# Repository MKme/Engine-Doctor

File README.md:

<p align="center">
<b>ESP32 Engine Doctor</b><br>
Use your smartphone web browser to view engine performance and sensor data<br><br>
<br>🐦 <a href="https://twitter.com/mkmeorg">Twitter</a>
| 📺 <a href="https://www.youtube.com/mkmeorg">YouTube</a>
| 🌍 <a href="http://www.mkme.org">mkme.org</a><br>
<br>
Support this project and become a patron on <a href="https://www.patreon.com/EricWilliam">Patreon</a>.<br>
Chat: <a href="https://discord.gg/j9S4Fgv">Discord</a></b>!
</p>

# DIY ESP32 Engine monitoring for all internal combustion engines 
Engine Doc for all chainsaws, small engines and automotive.  

Buy a kit on my store here: https://store.mkme.org/?product=diy-engine-doctor-esp32-egt-engine-tuning-temp-kit

## Use Case:
The original ideea is to use this for performance chainsaw tuning by monitoring the EGT (exhaust gas temp) or cylinder/head temp we have valuable information 
we can use to track/correlate our changes and even monitor saws with autotune or needs. 

## Description:

An ESP32 microcontroller with a high temp thermocouple interface you can mount in or stick to any surface you want to measure. 

The ESP32 makes its own Wifi AP (shows up as Engine Doctor wifi network) you can log in to with your phone- open any browser to the IP in the pic and it will graph the data real time asynchronously on the web page as long as its powered on.  

Also has a separate BME280 temp/baro and humidity sensor that will be in the box enclosure or you could remote mount it in an airbox or anywhere you desire.

Future Expansion- I may make a one-wire inductive tachometer pickup too which will be interrupt driven and may need amp circuit. All the spare GPIO are broken out on the PCB for this. 
Lipo battery plugs in to ESP32 and is charged by USB https://amzn.to/3kI5tL8

## Parts:

Buy a kit on my store here: https://store.mkme.org/?product=diy-engine-doctor-esp32-egt-engine-tuning-temp-kit

|     Component    | Source  |
| ---------- |----------------|
| ESP32 Wemos 32 Lite V1 | https://amzn.to/2QzS8t3
| MAX 6675 Thermocouple | https://amzn.to/3tyqds0
| BME280 | https://amzn.to/3x99uhg
| BMP280 (cheaper) | https://amzn.to/3kTSyYb

### Full video here:

https://www.youtube.com/watch?v=tzVUzIC2Xmo

### Assembly

- Solder BME 280- note SDC pin (furthest from VCC) is not used- Cut the pin or remove from header

- Use female headers (not supplied in kit) if you would like to make the components removeable

### Code

- Two flavours of code are now offered:

1.  BME280 Version- This has Temp, Pressure and HUMIDITY with Thermocouple

2.  BMP280 Version - This uses the cheaper BMP280 sensor without HUMIDITY

To upload the code you must install ESP32 board support- Google for tutorials

You must be using a fairly recent Arduino IDE to upload spiffs (the web page files)  

Set up your IDE using these settings for the board:

Upload the board (if you get any errors make sure you have installed the Adafruit libraries for the BMP or for BMP280: https://github.com/MartinL1/BMP280_DEV#bmp280_dev_library

Upload web page files Spiffs using the command "Tools> ESP32 Sketch Data Upload"

### How to Use It

- Install the thermocouple where you would like to monitor (use a magnet mount if desired) 

- Power on the EngineDoctor

- Connect to EngineDoctor Wifi with your phone or tablet (no password required)

- Open your web broswer to this url:  192.168.4.1

- Watch the live values in real time while you test/tune!

- Adjust the code if desired to alter the sample display rate (currently 1hz) 

### How I did things (reference) :

Export PCB Footprint to make a case in fusion: https://forum.kicad.info/t/kicad-to-dxf-or-dwg/7994/2

Make the case in fusion: https://www.youtube.com/watch?v=mhXUqtS4mDg&ab_channel=FixedUntilBroken

Make an awesome snap fit case - Thanks Noe! https://www.youtube.com/watch?v=VVmOtM60VWw&ab_channel=AdafruitIndustries

### ESP32 Pinout: 

This work is licensed under a Creative Commons Attribution-NonCommercial 4.0 International License. https://creativecommons.org/licenses/by-nc/4.0/ See comments in main code for more info

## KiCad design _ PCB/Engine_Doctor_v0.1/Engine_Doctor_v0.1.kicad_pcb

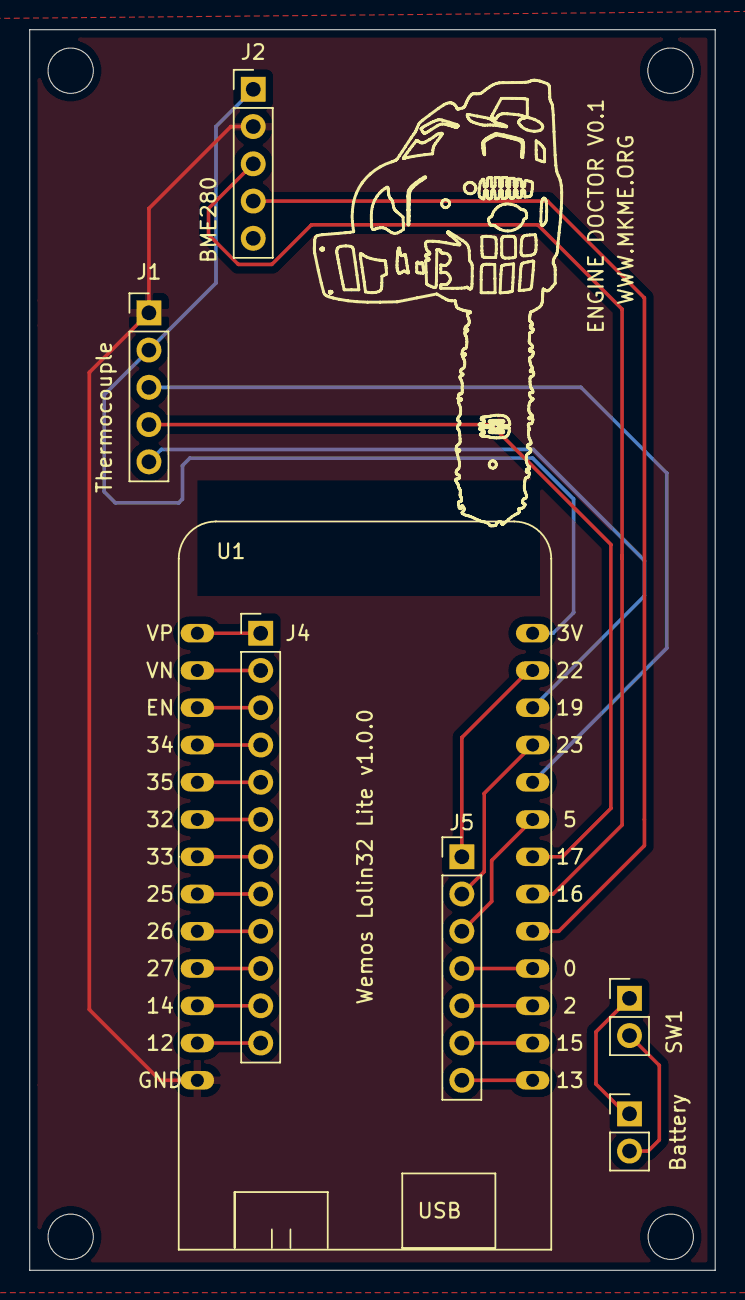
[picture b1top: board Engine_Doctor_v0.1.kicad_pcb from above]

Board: 2 copper layers, 46.7 x 84.6 mm, 7 parts (0 on the bottom side), 28 nets.

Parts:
J1: Thermocouple; PinHeader_1x05_P2.54mm_Vertical
J2: BME280; PinHeader_1x05_P2.54mm_Vertical
J3: Battery; PinHeader_1x02_P2.54mm_Vertical
J4: Spare2; PinHeader_1x12_P2.54mm_Vertical
J5: Spare1; PinHeader_1x07_P2.54mm_Vertical
SW1: Power Switch; PinHeader_1x02_P2.54mm_Vertical
U1: lolin32_lite_V1.00; lolin32_lite

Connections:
3v3: J1.2, J2.1, U1.26
CS: J1.4, U1.20
GND: J1.1, J2.2, U1.13
unnamed: J3.1, SW1.1
unnamed: J3.2, SW1.2
S0: J5.4, U1.17
S2: J5.5, U1.16
S5: J5.3, U1.21
S12: J4.12, U1.12
S13: J5.7, U1.14
S14: J4.11, U1.11
S15: J5.6, U1.15
S22: J5.1, U1.25
S23: J5.2, U1.23
S25: J4.8, U1.8
S26: J4.9, U1.9
S27: J4.10, U1.10
S32: J4.6, U1.6
S33: J4.7, U1.7
S34: J4.4, U1.4
S35: J4.5, U1.5
SCK: J1.3, U1.22
SCL: J2.3, U1.19
SDA: J2.4, U1.18
SEN: J4.3, U1.3
SO: J1.5, U1.24
SVN: J4.2, U1.2
SVP: J4.1, U1.1

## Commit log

2021-04-19 Ref files
2021-04-19 Ref added
2021-04-19 Working lib bak
2021-04-20 Revised alllllllllllllll
2021-04-21 Code buildz
2021-04-22 Temporarily disabled BME
    BME is what was crashing ESP- commented out triggers
2021-04-22 Cleanup
2021-04-23 Updated with Lolin board files
2021-04-28 Working BME 280 Code tested
2021-04-30 V0.1 PCB Design Complete
2021-04-30 PCB completed
2021-04-30 Code update comments
2021-05-02 pics
2021-07-24 Adding BMP280 Support
2021-07-24 Porting to BMP280
2021-07-24 BMP280 port working done like deener
2021-08-10 New case
2021-08-31 Comments updated - Released Done and dusted
2021-09-01 All the updatez belong to meee
